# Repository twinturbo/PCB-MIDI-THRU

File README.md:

# PCB-MIDI-THRU
https://electronics.stackexchange.com/questions/281467/midi-activity-led

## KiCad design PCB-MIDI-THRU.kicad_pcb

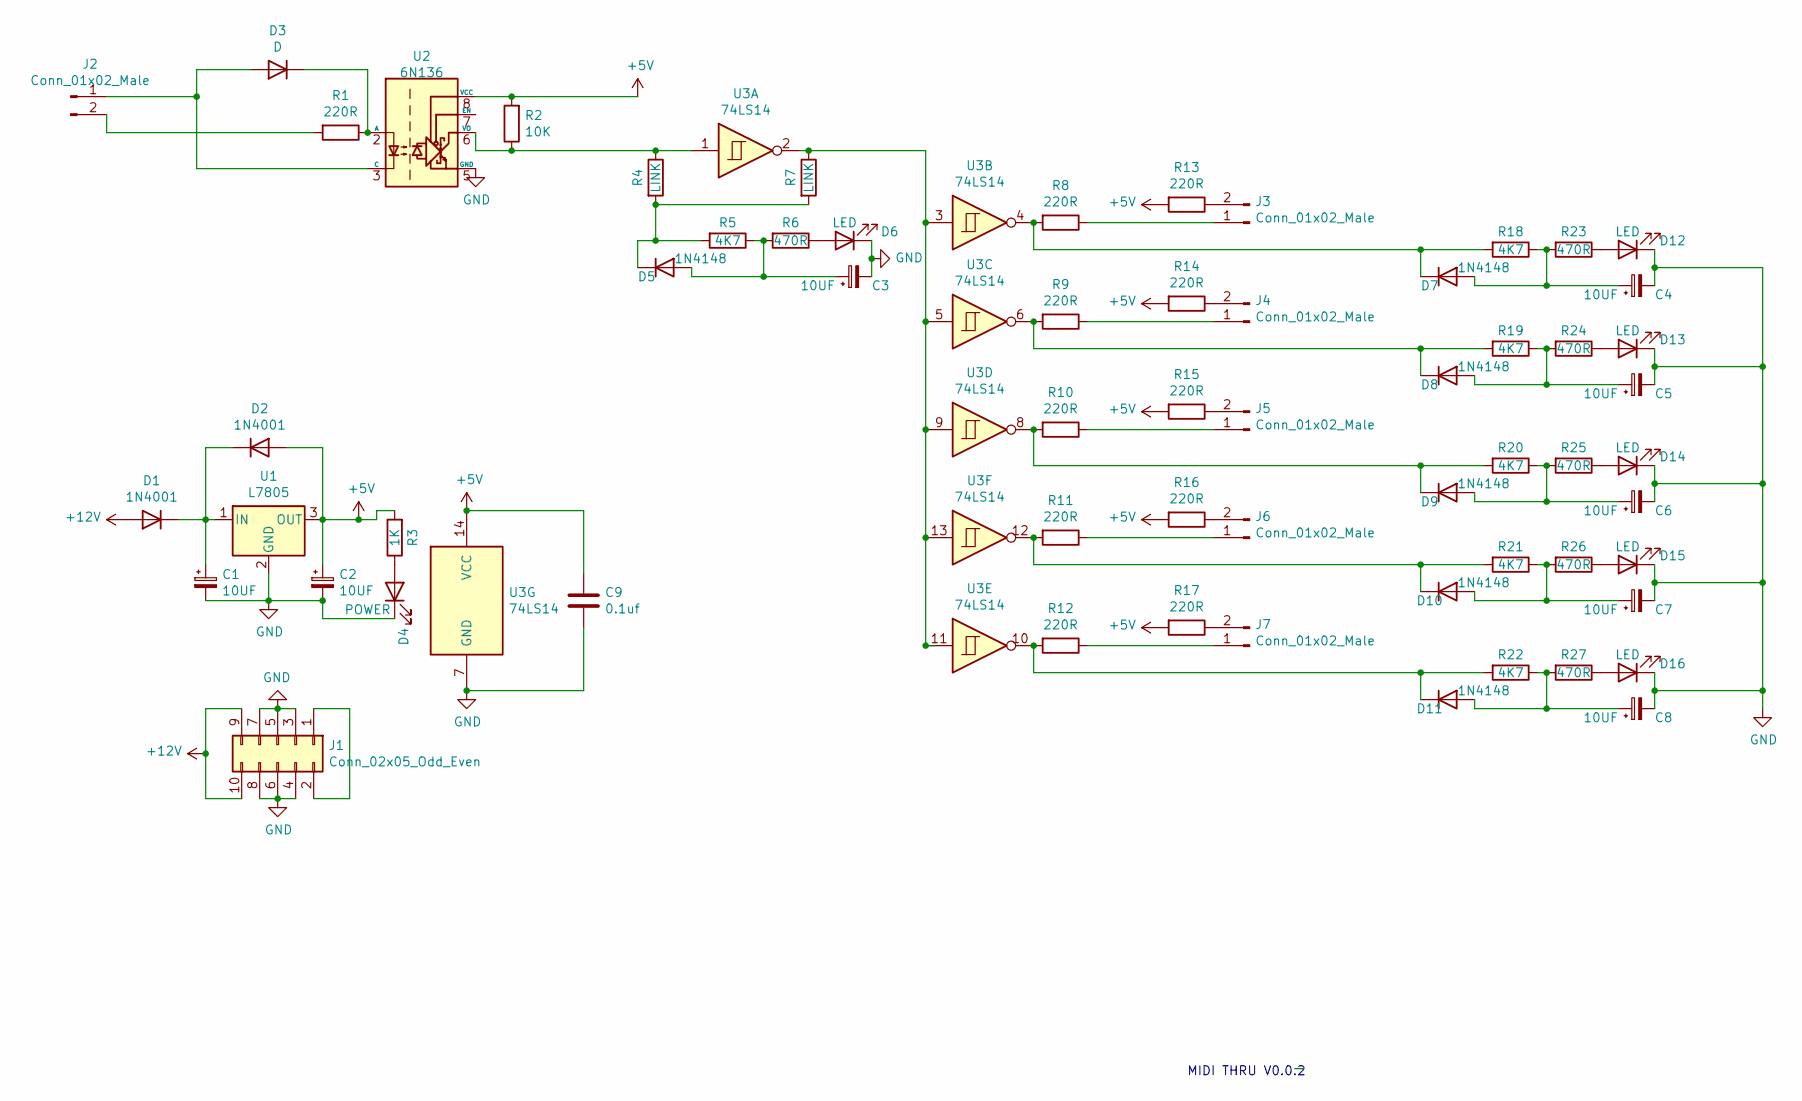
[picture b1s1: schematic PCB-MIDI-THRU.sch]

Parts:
C1, C2, C3, C4, C5, C6, C7, C8: 10UF; CP_Radial_D5.0mm_P2.50mm
C9: 0.1uf; C_Disc_D4.3mm_W1.9mm_P5.00mm
D1, D2: 1N4001; D_A-405_P10.16mm_Horizontal
D3: D; D_A-405_P10.16mm_Horizontal
D4: POWER; LED_D5.0mm
D5, D7, D8, D9, D10, D11: 1N4148; D_A-405_P10.16mm_Horizontal
D6, D12, D13, D14, D15, D16: LED; LED_D5.0mm
J1: Conn_02x05_Odd_Even; IDC-Header_2x05_P2.54mm_Vertical
J2, J3, J4, J5, J6, J7: Conn_01x02_Male; PinHeader_1x02_P2.54mm_Vertical
R1, R8, R9, R10, R11, R12, R13, R14, R15, R16, R17: 220R; R_Axial_DIN0207_L6.3mm_D2.5mm_P10.16mm_Horizontal
R2: 10K; R_Axial_DIN0207_L6.3mm_D2.5mm_P10.16mm_Horizontal
R3: 1K; R_Axial_DIN0207_L6.3mm_D2.5mm_P10.16mm_Horizontal
R4, R7: LINK; R_Axial_DIN0207_L6.3mm_D2.5mm_P10.16mm_Horizontal
R5, R18, R19, R20, R21, R22: 4K7; R_Axial_DIN0207_L6.3mm_D2.5mm_P10.16mm_Horizontal
R6, R23, R24, R25, R26, R27: 470R; R_Axial_DIN0207_L6.3mm_D2.5mm_P10.16mm_Horizontal
U1: L7805; TO-220-3_Horizontal_TabDown
U2: 6N136; DIP-8_W7.62mm
U3: 74LS14; DIP-14_W7.62mm

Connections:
+5V: C2.1, C9.1, D2.2 (A), R2.2, R3.2, R13.2, R14.2, R15.2, R16.2, R17.2, U1.3 (OUT), U2.8 (VCC), U3.14 (VCC)
+12V: D1.2 (A), J1.9, J1.10
GND: C1.2, C2.2, C3.2, C4.2, C5.2, C6.2, C7.2, C8.2, C9.2, D4.1 (K), D6.1 (K), D12.1 (K), D13.1 (K), D14.1 (K), D15.1 (K), D16.1 (K), J1.3, J1.4, J1.5, J1.6, J1.7, J1.8, U1.2 (GND), U2.5 (GND), U3.7 (GND)
unnamed: C1.1, D1.1 (K), D2.1 (K), U1.1 (IN)
unnamed: C3.1, D5.2 (A), R5.1, R6.2
unnamed: C4.1, D7.2 (A), R18.1, R23.2
unnamed: C5.1, D8.2 (A), R19.1, R24.2
unnamed: C6.1, D9.2 (A), R20.1, R25.2
unnamed: C7.1, D10.2 (A), R21.1, R26.2
unnamed: C8.1, D11.2 (A), R22.1, R27.2
unnamed: D3.1 (K), R1.1, U2.2 (A)
unnamed: D3.2 (A), J2.1, U2.3 (C)
unnamed: D4.2 (A), R3.1
unnamed: D5.1 (K), R4.2, R5.2, R7.2
unnamed: D6.2 (A), R6.1
unnamed: D7.1 (K), R8.2, R18.2, U3.4
unnamed: D8.1 (K), R9.2, R19.2, U3.6
unnamed: D9.1 (K), R10.2, R20.2, U3.8
unnamed: D10.1 (K), R11.2, R21.2, U3.12
unnamed: D11.1 (K), R12.2, R22.2, U3.10
unnamed: D12.2 (A), R23.1
unnamed: D13.2 (A), R24.1
unnamed: D14.2 (A), R25.1
unnamed: D15.2 (A), R26.1
unnamed: D16.2 (A), R27.1
unnamed: J1.1, J1.2
unnamed: J2.2, R1.2
unnamed: J3.1, R8.1
unnamed: J3.2, R13.1
unnamed: J4.1, R9.1
unnamed: J4.2, R14.1
unnamed: J5.1, R10.1
unnamed: J5.2, R15.1
unnamed: J6.1, R11.1
unnamed: J6.2, R16.1
unnamed: J7.1, R12.1
unnamed: J7.2, R17.1
unnamed: R2.1, R4.1, U2.6 (VO), U3.1
unnamed: R7.1, U3.2, U3.3, U3.5, U3.9, U3.11, U3.13

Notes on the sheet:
MIDI THRU V0.0.2

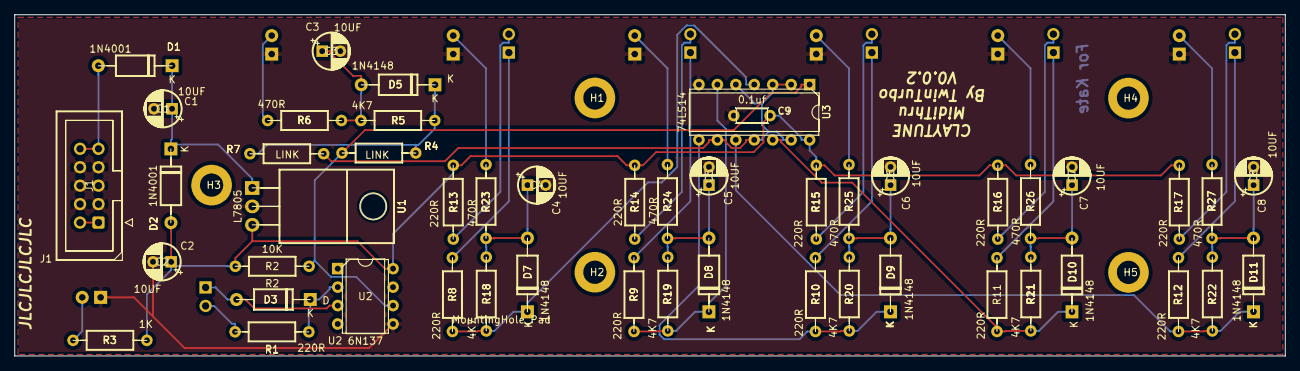
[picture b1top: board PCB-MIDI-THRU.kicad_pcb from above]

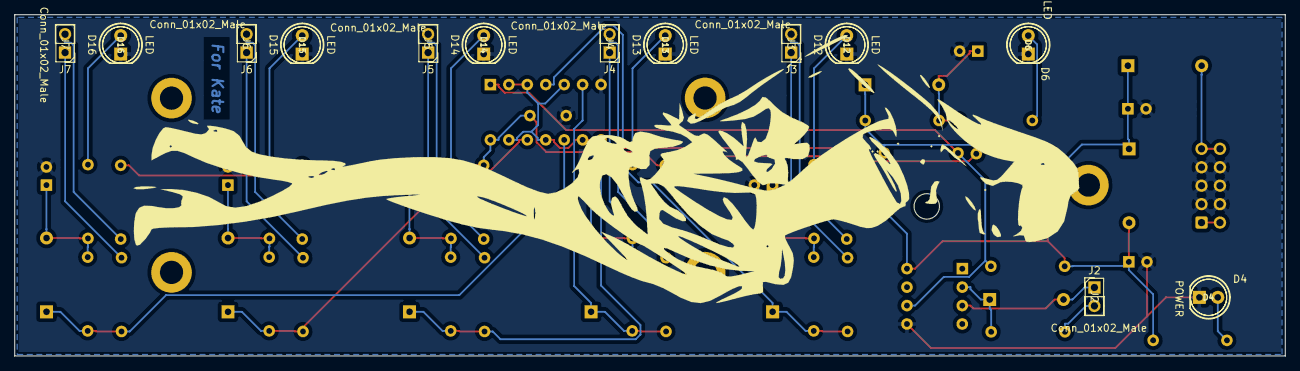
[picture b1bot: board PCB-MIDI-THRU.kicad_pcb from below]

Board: 2 copper layers, 175.0 x 47.0 mm, 67 parts (13 on the bottom side), 39 nets.

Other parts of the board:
H1, H2, H3, H4, H5: MountingHole_Pad; MountingHole_3.2mm_M3_DIN965_Pad

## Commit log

2021-02-14 Initialised
2021-02-14 autosync
2021-02-15 v0.0.1 PCB SCHEM
2021-02-15 v0.0.1 PCB SCHEM b
2021-02-15 v0.0.1 Front
2021-02-15 v0.0.1 pcb routed
2021-02-17 Layers
2022-01-30 Fixed PCB up to v0.0.2
2022-02-05 Removed input LED from SCH
2022-02-05 Mounting holes added to sche
2022-02-05 PCB minus input LED
2022-02-05 PCB V0.0.3
2022-02-05 FP - LED V0.0.3
2022-02-05 DOC Version Number Update
